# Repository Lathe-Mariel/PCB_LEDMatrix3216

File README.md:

# PCB_LEDMatrix3216

KiCAD: PCB data  
sample: sample projects for FPGA

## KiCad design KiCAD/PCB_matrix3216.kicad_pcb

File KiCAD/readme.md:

# files
output/  gerber data
sample/  sample software projects

# BoM
IC1 | NJM7805SDL1-TE1 | 5V regulater
IC2 | NJM2845DL1-33-TE1 | 3.3V Regulater
U1 | ドット抜けマトリクス | Matrix LED
J1 | 2DC-0415-B06 | 2.5mm標準DCジャック

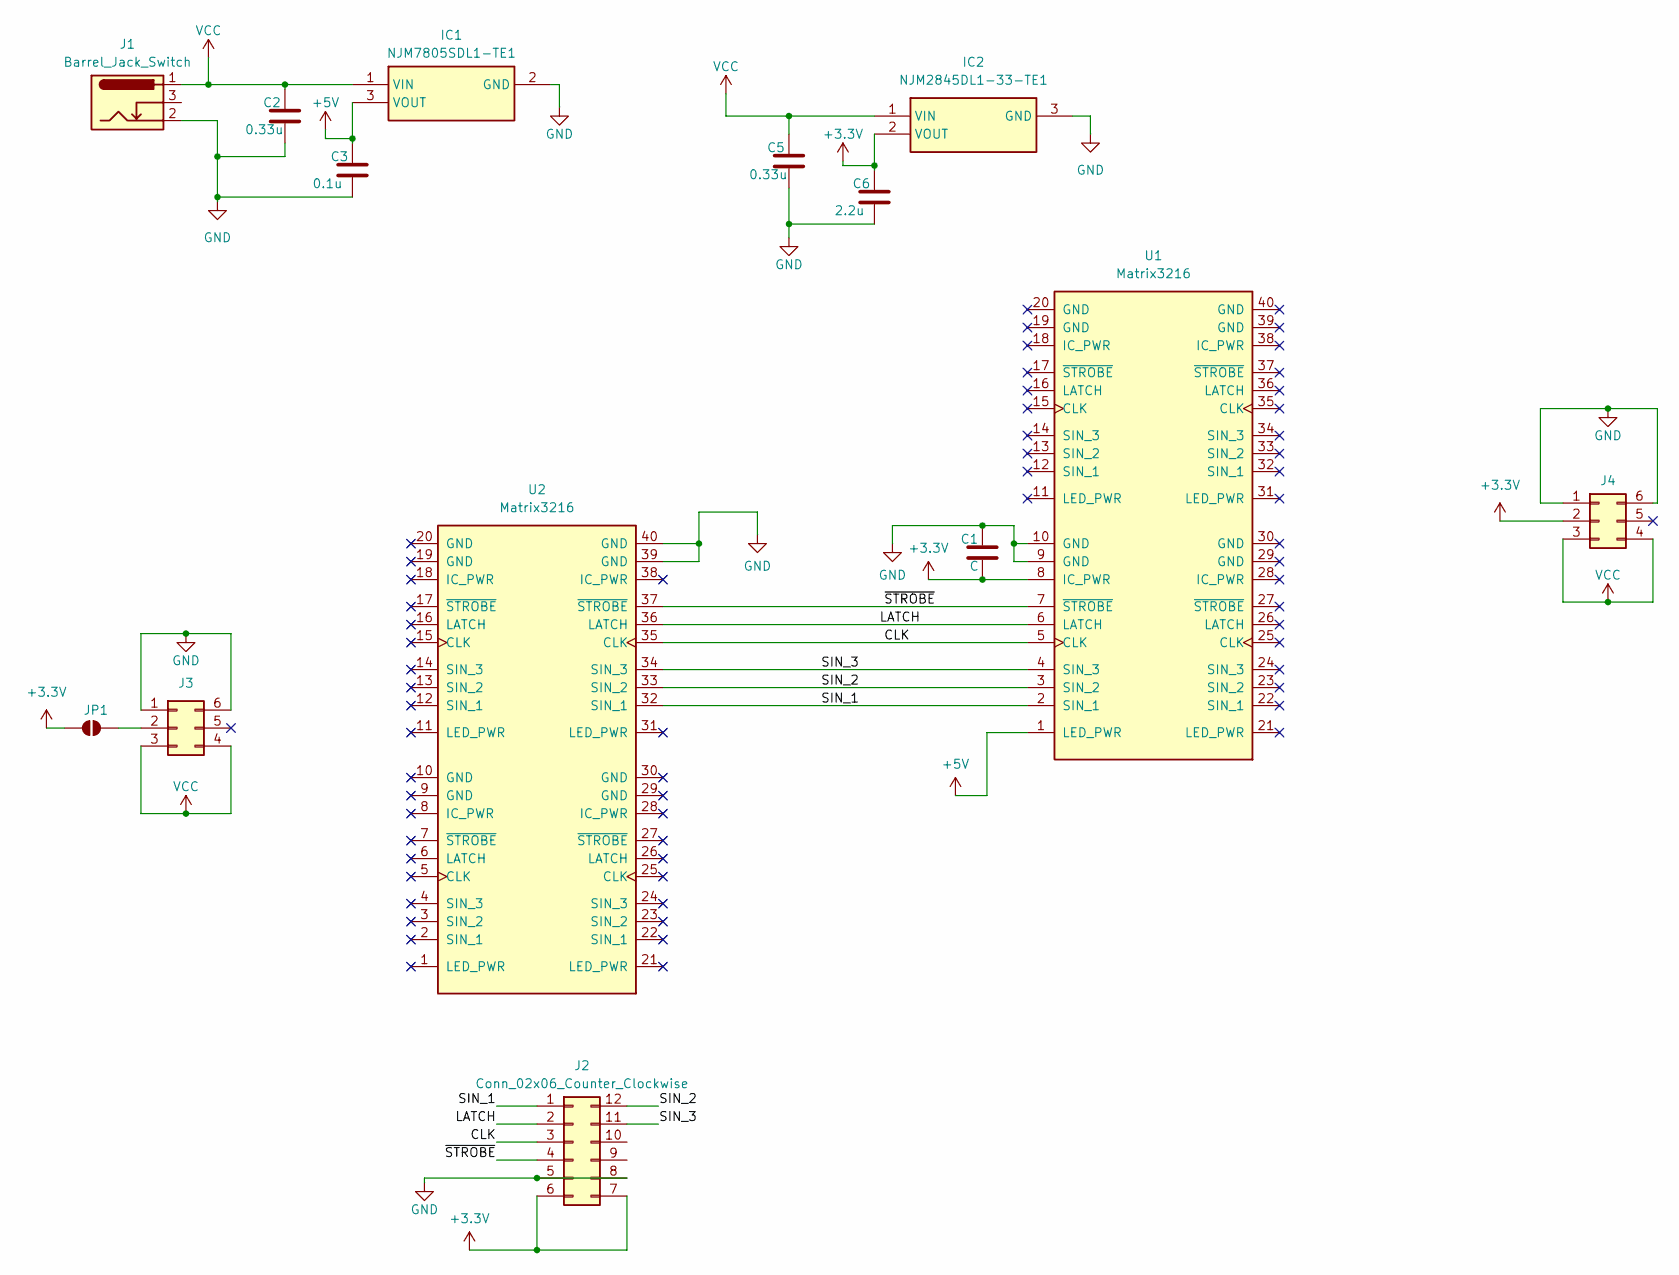
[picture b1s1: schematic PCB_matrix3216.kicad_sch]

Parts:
C1: C; C_0603_1608Metric_Pad1.08x0.95mm_HandSolder
C2, C5: 0.33u; C_0603_1608Metric_Pad1.08x0.95mm_HandSolder
C3: 0.1u; C_0603_1608Metric_Pad1.08x0.95mm_HandSolder
C6: 2.2u; C_0603_1608Metric_Pad1.08x0.95mm_HandSolder
IC1: NJM7805SDL1-TE1; NJM7805SDL1TE1; Manufacturer_Part_Number NJM7805SDL1-TE1
IC2: NJM2845DL1-33-TE1; TO-252-3-L1; Manufacturer_Part_Number NJM2845DL1-33-TE1
J1: Barrel_Jack_Switch; BarrelJack_CUI_PJ-036AH-SMT_Horizontal
J2: Conn_02x06_Counter_Clockwise; PinHeader_2x06_P2.54mm_Horizontal
J3: Conn_02x03_Counter_Clockwise; PinHeader_2x03_P2.54mm_Horizontal
J4: Conn_02x03_Counter_Clockwise; PinSocket_2x03_P2.54mm_Horizontal
JP1: SolderJumper_2_Open; SolderJumper-2_P1.3mm_Open_TrianglePad1.0x1.5mm
U1, U2: Matrix3216; matrix_led

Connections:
+3.3V: C1.2, C6.1, IC2.2 (VOUT), J2.6, J2.7, J4.2, JP1.1 (A), U1.8 (IC_PWR)
+5V: C3.1, IC1.3 (VOUT), U1.1 (LED_PWR)
/CLK: J2.3, U1.5 (CLK), U2.35 (CLK)
/LATCH: J2.2, U1.6 (LATCH), U2.36 (LATCH)
/SIN_1: J2.1, U1.2 (SIN_1), U2.32 (SIN_1)
/SIN_2: J2.12, U1.3 (SIN_2), U2.33 (SIN_2)
/SIN_3: J2.11, U1.4 (SIN_3), U2.34 (SIN_3)
/~STROBE: J2.4, U1.7 (~STROBE), U2.37 (~STROBE)
GND: C1.1, C2.2, C3.2, C5.2, C6.2, IC1.2 (GND), IC2.3 (GND), J1.2, J2.5, J2.8, J3.1, J3.6, J4.1, J4.6, U1.9 (GND), U1.10 (GND), U2.39 (GND), U2.40 (GND)
unnamed: J3.2, JP1.2 (B)
VCC: C2.1, C5.1, IC1.1 (VIN), IC2.1 (VIN), J1.1, J3.3, J3.4, J4.3, J4.4

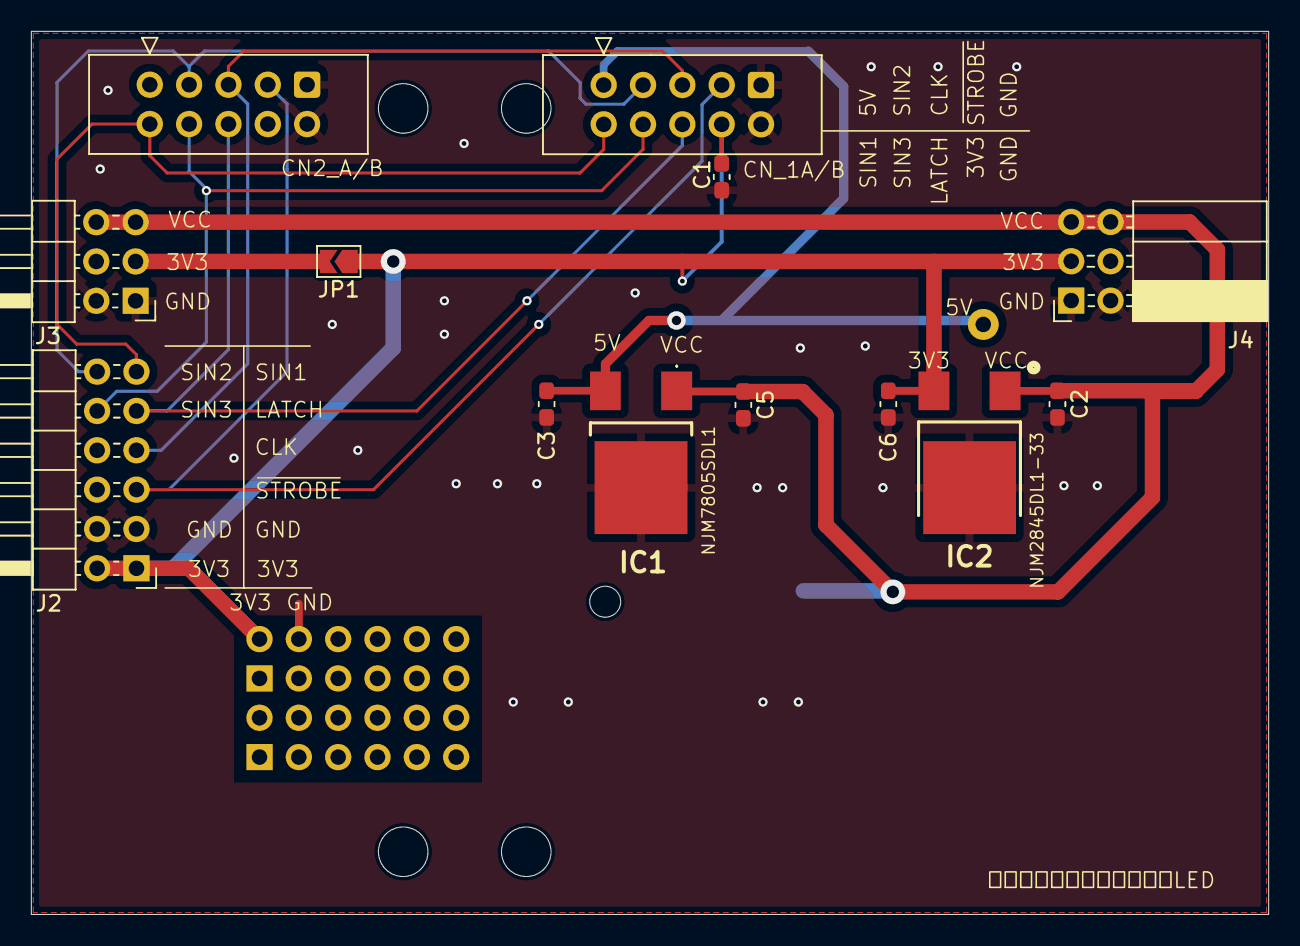
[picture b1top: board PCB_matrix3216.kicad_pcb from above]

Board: 2 copper layers, 79.9 x 57.0 mm, 14 parts (1 on the bottom side), 11 nets.

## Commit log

2026-03-26 0326
2026-03-30 schematics
2026-03-31 layout
2026-04-05 update pcb layout
2026-04-14 Artwork
2026-04-14 artwork revise
2026-04-15 Artwork done
2026-04-15 pcb done
2026-04-23 readme update
2026-04-25 sample project
2026-04-26 sample design of 6416matrix
2026-04-29 tetris
2026-04-29 tetris done
2026-04-29 Update README with KiCAD and sample project info
    Added sections for KiCAD and sample projects.
2026-04-29 Update README with FPGA sample project description
    Added a description for sample projects related to FPGA.
2026-05-13 veryl update
2026-05-13 sample veryl
2026-05-13 0514
2026-05-14 128x16 update
2026-05-14 veryl tetris
2026-05-14 0515
2026-05-15 veryl tetris controller edit
